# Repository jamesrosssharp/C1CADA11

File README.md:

# C1CADA11
C1CADA11 Handheld FPGA Gaming console

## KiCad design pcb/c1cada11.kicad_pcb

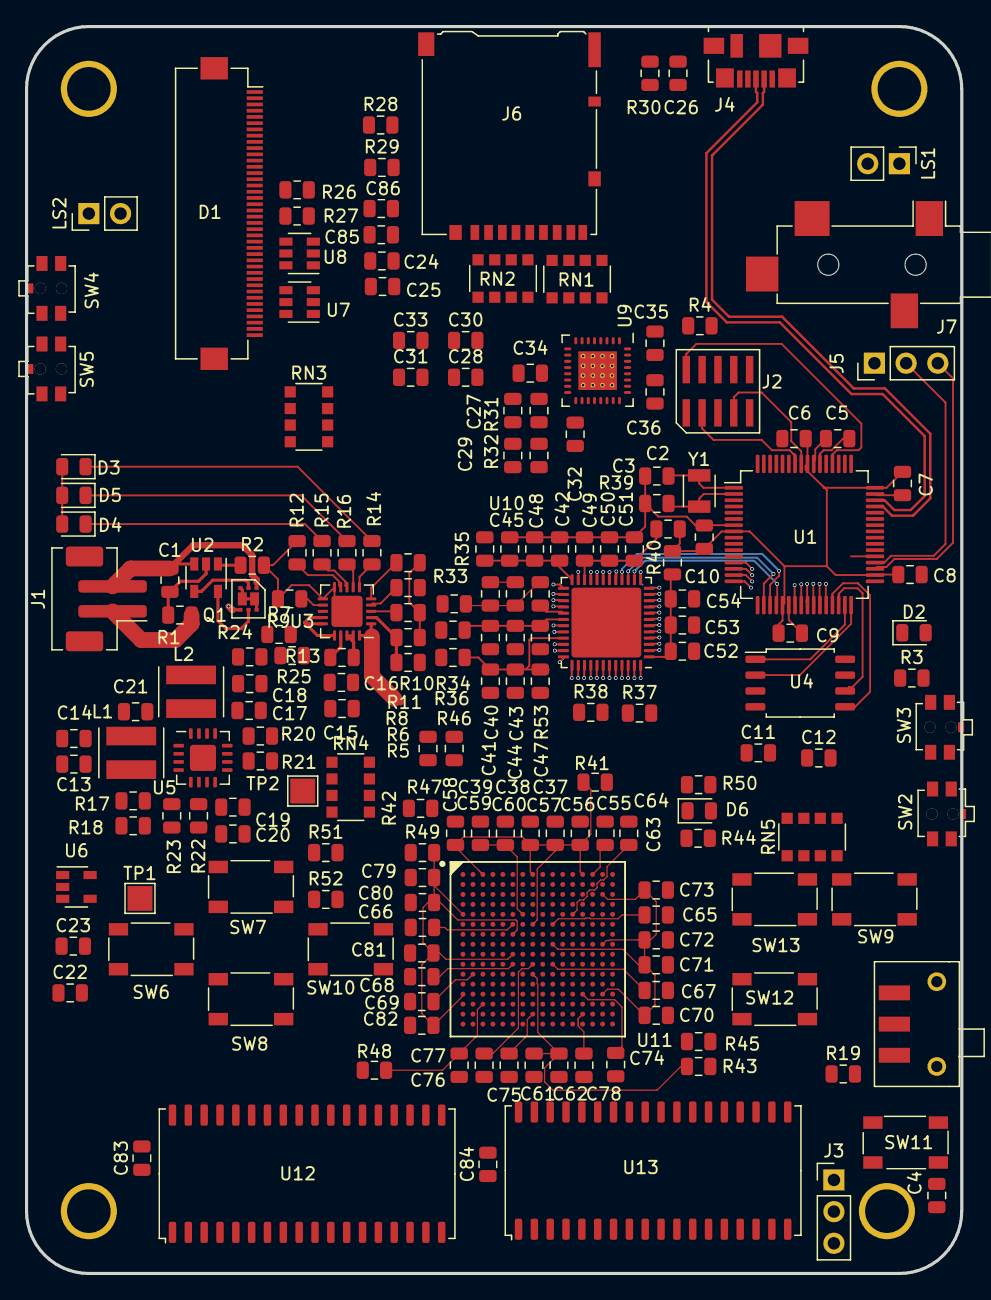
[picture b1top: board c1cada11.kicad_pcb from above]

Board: 4 copper layers, 75.0 x 100.0 mm, 194 parts (0 on the bottom side), 258 nets.

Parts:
C1, C16, C20, C25, C38, C43, C44, C45, C50, C53, C60, C62, C85, C86: 100nF; C_0805_2012Metric
C2, C3: 6.8pF; C_0805_2012Metric
C4, C6, C7, C8, C9, C10, C11, C12: 100n; C_0805_2012Metric
C5, C22, C23, C37, C41, C42, C49, C52: 1uF; C_0805_2012Metric
C13, C14, C15, C19, C21, C24, C40, C59, C61: 10uF; C_0805_2012Metric
C17: 100uF; C_0805_2012Metric
C18: 2.2uF; C_0805_2012Metric
C26: 4.7nF; C_0805_2012Metric
C27, C28, C29, C30, C31, C32, C33, C34, C35, C36, C55, C56, C57, C58, C63, C64, C65, C66, C67, C68, C69, C70, C71, C72, C73, C74, C75, C76, C77, C78, C79, C80, C81, C82, C83, C84: C; C_0805_2012Metric
C39, C47, C48, C51, C54: 10nF; C_0805_2012Metric
D1: 4DLCD-24320240-IPS; Hirose_FH12-40S-0.5SH_1x40-1MP_P0.50mm_Horizontal
D2, D3, D4, D5, D6: LED; LED_0805_2012Metric
J1: JSTBattCon; JST_PH_B2B-PH-SM4-TB_1x02-1MP_P2.00mm_Vertical
J2: Conn_ARM_JTAG_SWD_10; FTSH10501
J3, J5: Conn_01x03_Male; PinHeader_1x03_P2.54mm_Vertical
J4: USB_B_Micro; USB_Micro-B_Molex_47346-0001
J6: Micro_SD_Card; microSD_HC_Hirose_DM3AT-SF-PEJM5
J7: CUI3524; Jack_3.5mm_CUI_SJ-3524-SMT_Horizontal
L1, L2: 22uH; TYS4030220M-10
LS1, LS2: CDM-20008; PinHeader_1x02_P2.54mm_Vertical
Q1: PMDPB30XN
R1: 330R; R_0805_2012Metric
R2: 2k7; R_0805_2012Metric
R3, R4, R14, R15, R16: 1k; R_0805_2012Metric
R5: 330k; R_0805_2012Metric
R6: 110k; R_0805_2012Metric
R7: 2k; R_0805_2012Metric
R8, R10, R11, R12, R13, R19, R20, R28: 10k; R_0805_2012Metric
R9: 100k; R_0805_2012Metric
R17: 1M8; R_0805_2012Metric
R18: 390k; R_0805_2012Metric
R21, R24, R30: 1M; R_0805_2012Metric
R22: 250k; R_0805_2012Metric
R23: 180k; R_0805_2012Metric
R25: 180k'; R_0805_2012Metric
R26, R27: 15k; R_0805_2012Metric
R29: 10k DNF; R_0805_2012Metric
R31, R32, R37, R38, R46, R47, R50: R_Small; R_0805_2012Metric
R33, R34, R35, R36, R39, R40, R41, R44, R45, R48, R49: 1R; R_0805_2012Metric
R42, R43: 100R; R_0805_2012Metric
R51, R52: 0R; R_0805_2012Metric
R53: 100; R_0805_2012Metric
RN1, RN2, RN3, RN4, RN5: 10k; R_Array_Convex_4x1206
SW1: JS102011SAQN SPDT; JS102011SAQN
SW2, SW3, SW4, SW5: SW_Push; PTS841-GM-SMTR
SW6, SW7, SW8, SW9, SW10, SW11, SW12, SW13: SW_Push; PTS647SN50SMTR2LFS
TP1, TP2: TestPoint; TestPoint_Pad_2.0x2.0mm
TP3, TP4, TP5, TP6: TestPoint; M3-HOLE
U1: ATSAMD21J18A-A; TQFP-64_10x10mm_P0.5mm
U2: AP9101CK; SOT-23-5
U3: MCP73871-2AA; QFN-20-1EP_4x4mm_P0.5mm_EP2.5x2.5mm
U4: W25Q128JVS; SOIC-8_5.23x5.23mm_P1.27mm
U5: TPS61130RSA; QFN-16-1EP_4x4mm_P0.65mm_EP2.1x2.1mm
U6: MIC5504-2.5YM5; SOT-23-5
U7, U8: MIC2860-2D; SOT-23-6
U9: LM49450; QFN-32_EP_5.4x5.4_Pitch0.5mm
U10: ICE40UP5K-SG48ITR; QFN-48-1EP_7x7mm_P0.5mm_EP5.6x5.6mm
U11: iCE40-HX8K-CT256; Lattice_Semiconductor-ICE40HX8K-CT256-Manufacturer_Recommen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
U12, U13: IS61C5128AL-10KLI; SOJ-36_10.16x23.49mm_P1.27mm
Y1: CM7T1A 32.768kHz; CM7V-T1A

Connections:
8K_CDONE: R46.2, U1.14, U11.M10
8K_MISO: U1.28, U11.P12
8K_MOSI: U1.25, U11.P11
8K_RESETb: R47.1, U1.13, U11.N11
8K_SCK: U1.26, U11.R11
8K_SS: U1.27, U11.R12
8K_UC1: U1.23, U11.J4
8K_UC02: U1.3, U11.H2
8K_UC3: U1.4, U11.J5
+1V2: R33.1, R34.1, R42.2, R43.2, R44.2, R51.1
+2V5: C23.1, C28.1, C30.1, C63.2, R35.1, U6.5, U9.28, U9.32
+3V3: C6.1, C7.1, C8.1, C9.1, C10.1, C11.1, C12.1, C22.1, C24.1, C25.1, C31.1, C33.1, C74.1, C83.1, C84.1, C85.1, C86.1, D1.12, D1.33, D2.2, D6.2, J2.1, J6.4, R4.2, R20.1, R21.1, R28.1, R36.1, R39.1, R40.1, R41.1, R45.1, R48.1, R49.1, R52.1, RN1.5, RN1.6, RN1.7, RN1.8, RN2.5, RN2.6, RN2.7, RN2.8, RN3.5, RN3.6, RN3.7, RN3.8, RN4.5, RN4.6, RN4.7, RN4.8, RN5.5, RN5.6, RN5.7, RN5.8, U1.8, U1.21, U1.34, U1.48, U1.56, U4.8, U5.6, U5.7, U6.1, U6.3, U7.3, U8.3, U9.10, U9.11, U9.16, U9.18, U9.24, U11.N13, U12.9, U12.27, U13.9, U13.27
/FPGA2/VCC: C64.2, C65.2, C66.2, C67.1, C68.2, C69.2, R44.1, U11.A14, U11.F6, U11.F10, U11.K6, U11.K10, U11.L2
/MicroController/FLASH_IO2: U1.15, U4.3
/MicroController/FLASH_IO3: U1.16, U4.7
/MicroController/FLASH_MISO: U1.32, U4.2
/MicroController/FLASH_MOSI: U1.29, U4.5
/MicroController/FLASH_SCK: U1.30, U4.6
/MicroController/FLASH_SS: U1.31, U4.1
/MicroController/SWCLK: J2.4, R4.1, U1.57
/MicroController/SWDIO: J2.2, U1.58
/Power/1V2_OUT: C19.1, C20.1, R22.1, R51.2, TP1.1, U5.8
/Power/3V3_OUT: C17.1, C18.1, R24.2, R52.2, TP2.1, U5.14
/Power/EN_REG: R19.1, SW1.2, U5.5
/Power/VBAT: J1.1, R1.2, U3.14, U3.15, U3.16
A: RN5.1, SW13.1, U11.H13
AUDIO_I2S_CLK: U9.7, U11.M13
AUDIO_I2S_SDI: U9.6, U11.M14
AUDIO_MCLK: U9.8, U11.P16
AUDIO_PWM_L: R32.2, U11.P15
AUDIO_PWM_R: R31.2, U11.P14
AUDIO_SCK: RN1.2, U9.9, U11.L13
AUDIO_SDA: RN1.1, U9.3, U11.N16
B: RN5.2, SW12.1, U11.A9
BDOWN: RN3.2, SW3.2, U11.J15
BOOTLDR: RN5.3, SW9.1, U1.43
BUP: RN3.1, SW2.2, U11.K14
DISP_CS: D1.9, U11.D13
DISP_D0: D1.25, U11.A10
DISP_D1: D1.26, U11.A11
DISP_D2: D1.27, U11.D10
DISP_D3: D1.28, U11.C9
DISP_D4: D1.29, U11.E9
DISP_D5: D1.30, U11.D9
DISP_D6: D1.24, U11.C10
DISP_D7: D1.23, U11.B11
DISP_D8: D1.22, U11.B10
DISP_D9: D1.21, U11.B12
DISP_D10: D1.20, U11.D11
DISP_D11: D1.19, U11.C11
DISP_D12: D1.18, U11.E10
DISP_D13: D1.17, U11.B13
DISP_D14: D1.16, U11.A15
DISP_D15: D1.15, U11.A16
DISP_FMARK: D1.4, U11.C13
DISP_IM0: D1.3, R28.2, R29.1, U11.R15
DISP_RD: D1.10, U11.B14
DISP_RS: D1.8, U11.B15
DISP_RST: D1.7, U11.C14
DISP_RW: D1.11, U11.C12
DISP_SC: U7.1, U8.1
DISP_SDI: D1.2, U11.R14
DISP_SDO: D1.13, U11.E11
DOWN: RN4.3, SW8.2, U11.J13
FPGA_DA0: U10.25, U11.P5
FPGA_DA1: U10.23, U11.R3
FPGA_DA2: U10.27, U11.R5
FPGA_DA3: U10.26, U11.T3
FPGA_DA4: U10.28, U11.R4
FPGA_DA5: U10.31, U11.M7
FPGA_DA6: U10.32, U11.N7
FPGA_DA7: U10.34, U11.P6
FPGA_DA8: U10.37, U11.M8
FPGA_DA9: U10.35, U11.T5
FPGA_DA10: U10.36, U11.R6
FPGA_DA11: U10.43, U11.P8
FPGA_DA12: U10.38, U11.T6
FPGA_DA13: U10.42, U11.L9
FPGA_DA14: U10.6, U11.T7
FPGA_DA15: U10.9, U11.T8
FPGA_DA16: U10.10, U11.P7
FPGA_DA17: U10.11, U11.N9
FPGA_DA18: U10.12, U11.T9
FPGA_DA19: U10.21, U11.M9
FPGA_DA20: U10.13, U11.P9
FPGA_DA21: U10.20, U11.R10
FPGA_DA22: U10.19, U11.L10
FPGA_DA23: U10.18, U11.P10
FPGA_DA24: U10.46, U11.N10
FPGA_DA25: U10.47, U11.T10
FPGA_DA26: U10.44, U11.T11
FPGA_DA27: U10.48, U11.T15
FPGA_DA28: U10.45, U11.T14
FPGA_DA29: U10.2, U11.M11
FPGA_DA30: U10.4, U11.T13
FPGA_DA31: U10.3, U11.N12
FPGA_UART_RX: J3.2, U11.L16
FPGA_UART_TX: J3.3, U11.K13
GND: C2.2, C3.2, C4.2, C5.2, C6.2, C7.2, C8.2, C9.2, C10.2, C11.2, C12.2, C13.2, C14.2, C15.2, C16.2, C17.2, C18.2, C19.2, C20.2, C22.2, C23.2, C24.2, C25.2, C26.2, C27.2, C28.2, C29.2, C30.2, C31.2, C32.2, C33.2, C34.2, C36.2, C37.2, C38.2, C39.2, C40.2, C41.2, C42.2, C43.2, C44.2, C45.2, C47.2, C48.2, C49.2, C50.2, C51.2, C52.2, C53.2, C54.2, C55.2, C56.2, C57.2, C58.2, C64.1, C65.1, C66.1, C67.2, C68.1, C69.1, C70.2, C71.2, C72.2, C73.2, C74.2, C75.2, C76.2, C77.2, C78.2, C79.2, C80.2, C81.2, C82.2, C83.2, C84.2, C85.2, C86.2, D1.1, D1.14, D1.40, J2.3, J2.5, J2.9, J3.1, J4.5, J5.1, J6.6, J6.9, J7.S, L2.2, Q1.4, R2.2, R6.2, R7.2, R8.2, R9.2, R10.2, R12.2, R18.2, R19.2, R23.2, R25.2, R26.2, R27.2, R29.2, R30.2, R37.2, R47.2, SW2.1, SW3.1, SW4.1, SW5.1, SW6.1, SW7.2, SW8.1, SW9.2, SW10.2, SW11.2, TP3.1, TP4.1, TP5.1, TP6.1, U1.7, U1.22, U1.33, U1.47, U1.54, U3.10, U3.11, U3.21, U4.4, U5.1, U5.10, U6.2, U7.2, U8.2, U9.2, U9.4, U9.12, U9.21, U9.25, U10.49, U11.A4, U11.A12, U11.E15, U11.G7, U11.G8, U11.G9, U11.H7, U11.H8, U11.H9, U11.J7, U11.J8, U11.J9, U11.K2, U11.K7, U11.L15, U11.R7, U11.T4, U11.T12, U12.10, U12.28, U13.10, U13.28
I2S_WS: U9.5, U11.L12
LBOb: R21.2, U1.63, U5.11
LEFT: RN4.1, SW6.2, U11.J14
unnamed: C1.1, J1.2, Q1.1, U2.3
unnamed: C1.2, R1.1, U2.2
unnamed: C2.1, U1.1, Y1.1
unnamed: C3.1, U1.2, Y1.2
unnamed: C5.1, U1.55
unnamed: C13.1, C14.1, L1.1, R17.1, SW1.1, U3.1, U3.20, U5.2, U5.4
unnamed: C21.1, L2.1, U5.15
unnamed: C21.2, L1.2, U5.16
unnamed: C26.1, J4.6, R30.1
unnamed: C27.1, R31.1, U9.14
unnamed: C29.1, R32.1, U9.15
unnamed: C32.1, U9.17
unnamed: C34.1, U9.13
unnamed: C35.1, U9.31
unnamed: C35.2, U9.1
unnamed: C36.1, U9.30
unnamed: C37.1, C38.1, C39.1, R36.2, U10.33
unnamed: C40.1, C43.1, R33.2, R53.2
unnamed: C41.1, C44.1, C47.1, R34.2, U10.5, U10.30
unnamed: C42.1, C45.1, C48.1, R35.2, U10.24
unnamed: C49.1, C50.1, C51.1, R38.1, R39.2, U10.22
unnamed: C52.1, C53.1, C54.1, R40.2, U10.1
unnamed: C55.1, C56.1, C57.1, C58.1, R41.2, U11.A3, U11.A8, U11.A13, U11.F8
unnamed: C59.1, C60.1, U11.E7
unnamed: C59.2, C60.2, R42.1, U11.E8
unnamed: C61.1, C62.1, U11.N8
unnamed: C61.2, C62.2, R43.1, U11.L8
unnamed: C63.1, U11.E12
unnamed: C70.1, C71.1, C72.1, C73.1, R45.2, U11.C15, U11.H10, U11.H15, U11.N15
unnamed: C75.1, C76.1, C77.1, C78.1, R46.1, R48.2, U11.K8, U11.P3, U11.R8, U11.R13
unnamed: C79.1, C80.1, C81.1, C82.1, R49.2, U11.E1, U11.G6, U11.J6, U11.N1
unnamed: D1.34, U8.6
unnamed: D1.35, U8.4
unnamed: D1.36, U7.6
unnamed: D1.37, U7.4
unnamed: D2.1, R3.1
unnamed: D3.1, R14.1
unnamed: D4.1, R15.1
unnamed: D5.1, R16.1
unnamed: D6.1, R50.1
unnamed: J7.R, U9.27
unnamed: J7.T, U9.29
unnamed: J7.TN, U9.26
unnamed: LS1.1, U9.19
unnamed: LS1.2, U9.20
unnamed: LS2.1, U9.23
unnamed: LS2.2, U9.22
unnamed: Q1.2, U2.4
unnamed: Q1.3, Q1.6, Q1.7, Q1.8
unnamed: Q1.5, U2.5
unnamed: R2.1, U2.1
unnamed: R3.2, U1.61
unnamed: R5.2, R6.1, U3.2
unnamed: R7.1, U3.13
unnamed: R8.1, U3.3
unnamed: R9.1, U3.12
unnamed: R10.1, U3.5
unnamed: R11.1, U3.4
unnamed: R12.1, U3.9
unnamed: R13.1, U3.17
unnamed: R14.2, U3.6
unnamed: R15.2, U3.8
unnamed: R16.2, U3.7
unnamed: R17.2, R18.1, U5.3
unnamed: R22.2, R23.1, U5.9
unnamed: R24.1, R25.1, U5.13
unnamed: R26.1, U8.5
unnamed: R27.1, U7.5
unnamed: R50.2, U11.K5
unnamed: R53.1, U10.29
PGb: R20.2, U1.62, U5.12
R0_A0: U11.H14, U12.1
R0_A1: U11.G16, U12.2
R0_A2: U11.H12, U12.3
R0_A3: U11.G15, U12.4
R0_A4: U11.G10, U12.5
R0_A5: U11.F16, U12.14
R0_A6: U11.G11, U12.15
R0_A7: U11.F15, U12.16
R0_A8: U11.G14, U12.17
R0_A9: U11.E16, U12.18
R0_A10: U11.G13, U12.20
R0_A11: U11.D16, U12.21
R0_A12: U11.G12, U12.22
R0_A13: U11.F14, U12.23
R0_A14: U11.F12, U12.24
R0_A15: U11.D15, U12.32
R0_A16: U11.F11, U12.33
R0_A17: U11.E14, U12.34
R0_A18: U11.C16, U12.35
R0_CEb: U11.F13, U12.6
R0_D0: U11.T2, U12.7
R0_D1: U11.N5, U12.8
R0_D2: U11.R2, U12.11
R0_D3: U11.P4, U12.12
R0_D4: U11.T1, U12.25
R0_D5: U11.N6, U12.26
R0_D6: U11.T16, U12.29
R0_D7: U11.L11, U12.30
R0_OEb: U11.B16, U12.31
R0_WEb: U11.E13, U12.13
R1_A0: U11.E4, U13.1
R1_A1: U11.B2, U13.2
R1_A2: U11.F5, U13.3
R1_A3: U11.B1, U13.4
R1_A4: U11.C1, U13.5
R1_A5: U11.C2, U13.14
R1_A6: U11.F4, U13.15
R1_A7: U11.D2, U13.16
R1_A8: U11.G5, U13.17
R1_A9: U11.D1, U13.18
R1_A10: U11.G4, U13.20
R1_A11: U11.E3, U13.21
R1_A12: U11.H5, U13.22
R1_A13: U11.E2, U13.23
R1_A14: U11.G3, U13.24
R1_A15: U11.F3, U13.32
R1_A16: U11.H3, U13.33
R1_A17: U11.F2, U13.34
R1_A18: U11.H6, U13.35
R1_CEb: U11.F1, U13.6
R1_D0: U11.H1, U13.7
R1_D1: U11.J2, U13.8
R1_D2: U11.J1, U13.11
R1_D3: U11.K1, U13.12
R1_D4: U11.K3, U13.25
R1_D5: U11.L4, U13.26
R1_D6: U11.L1, U13.29
R1_D7: U11.K4, U13.30
R1_OEb: U11.H4, U13.31
R1_WEb: U11.G2, U13.13
RESET: C4.1, J2.10, RN5.4, SW11.1, U1.52
RIGHT: RN4.4, SW10.1, U11.J16
SD_CLK: J6.5, RN2.1, U11.J10
SD_CMD: J6.3, RN2.2, U11.M16
SD_DAT0: J6.7, RN1.4, U11.M15
SD_DAT1: J6.8, RN1.3, U11.J11
SD_DAT2: J6.1, RN2.4, U11.L14
SD_DAT3: J6.2, RN2.3, U11.K12
UC_UART_RX: J5.2, U1.36
UC_UART_TX: J5.3, U1.35
UP: RN4.2, SW7.1, U11.J12
UP5K_CDONE: R38.2, U1.42, U10.7
UP5K_MISO: U1.20, U10.14
UP5K_MOSI: U1.17, U10.17
UP5K_RESETb: R37.1, U1.41, U10.8
UP5K_SCK: U1.18, U10.15
UP5K_SS: U1.19, U10.16
UP5K_UC1: U1.24, U10.41
UP5K_UC2: U1.38, U10.40
UP5K_UC3: U1.37, U10.39
USB_D+: J4.3, U1.46
USB_D-: J4.2, U1.45
VDOWN: RN3.3, SW5.2, U11.K15
VUP: RN3.4, SW4.2, U11.K16
VUSB_5V: C15.1, C16.1, D3.2, D4.2, D5.2, R5.1, R11.2, R13.2, U3.18, U3.19

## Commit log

2020-09-27 Added files
